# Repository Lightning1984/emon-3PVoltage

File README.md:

emon-3PVoltage
==============

Open Energy Monitoring 3 Phase Voltage Sensing Hardware with optoisolated I²C Interface

Images of the finished device can be found here:
<table style="width:194px;"><tr><td align="center" style="height:194px;background:url(https://www.gstatic.com/pwa/s/v/lighthousefe_241.01/transparent_album_background.gif) no-repeat left"></td></tr><tr><td style="text-align:center;font-family:arial,sans-serif;font-size:11px"><a href="https://picasaweb.google.com/rdobroun/Emon3PVoltage?authuser=0&feat=embedwebsite" style="color:#4D4D4D;font-weight:bold;text-decoration:none;">Emon3PVoltage</a></td></tr></table>

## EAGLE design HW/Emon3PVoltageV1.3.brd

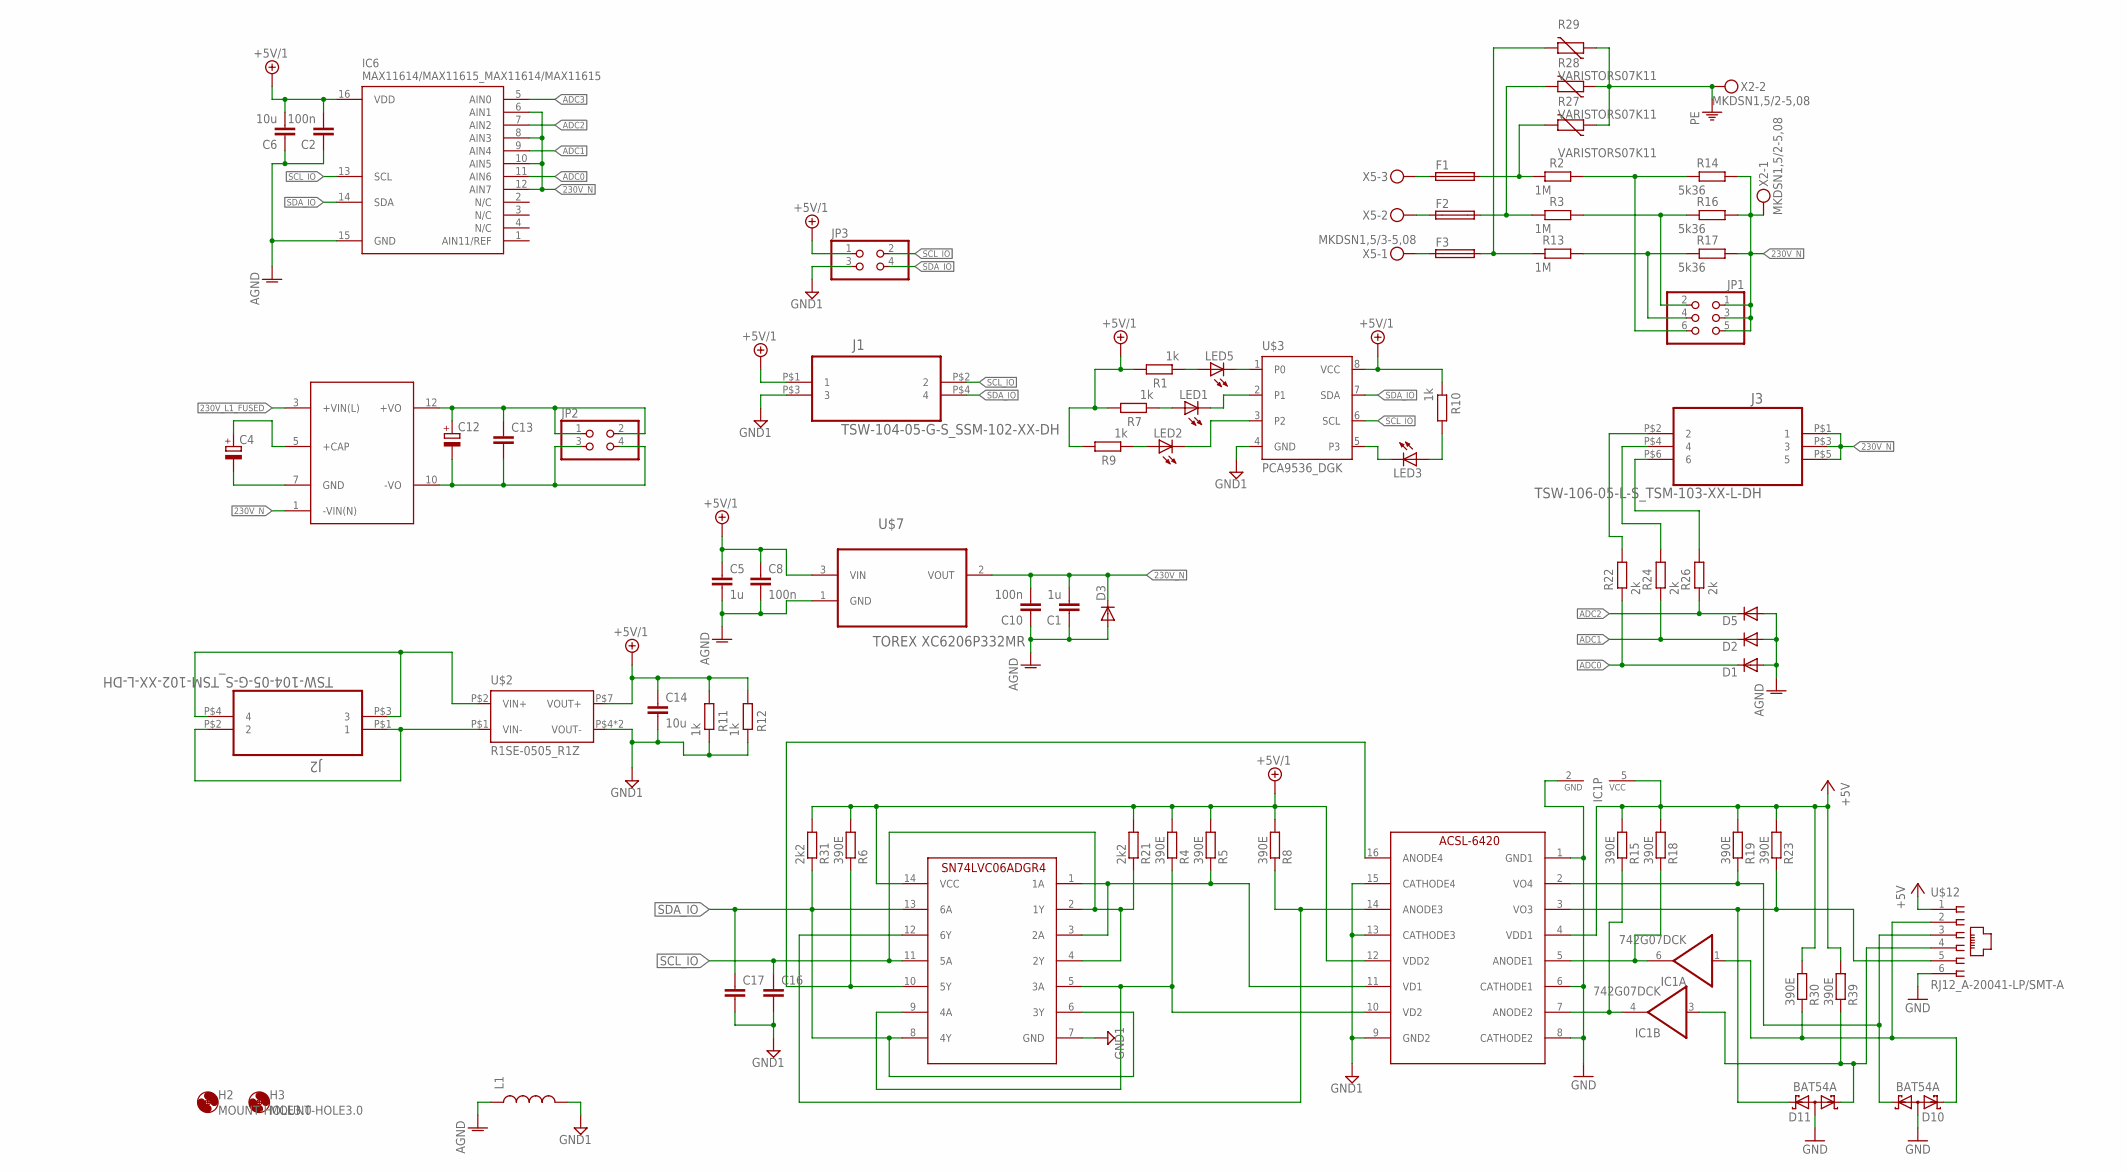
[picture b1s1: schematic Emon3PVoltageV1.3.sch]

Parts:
C1, C5: 1u; C0805
C2, C8, C10: 100n; C0805
C4: CPOL-EUE5-13; E5-13
C6, C14: 10u; C0805
C12: CPOL-EUE5-10.5; E5-10,5
C13, C16, C17: C-EUC0805; C0805
D1, D2, D3, D5: DIODE-SOD523; SOD523
D10, D11: BAT54A; SOT23
F1, F2, F3: TE5
H2, H3: MOUNT-HOLE3.0; 3,0
IC1: 742G07DCK; SC70-6
IC6: MAX11614/MAX11615_MAX11614/MAX11615; QSOP16_2
J1: TSW-104-05-G-S_SSM-102-XX-DH; SAMTEC_SSM-102-XX-DH
J2: TSW-104-05-G-S_TSM-102-XX-L-DH; SAMTEC_TSM-102-XX-L-DH
J3: TSW-106-05-L-S_TSM-103-XX-L-DH; SAMTEC_TSM-103-XX-L-DH
JP1: PINHD-2X3; 2X03
JP2, JP3: PINHD-2X2; 2X02
L1: INDUCTOR0805; 0805
LED1, LED2, LED3, LED5: LEDCHIPLED_1206; CHIPLED_1206
R1, R7, R9, R10, R11, R12: 1k; R1206
R2, R3, R13: 1M; 0207/12
R4, R5, R6, R8, R15, R18, R19, R23, R30, R39: 390E; R1206
R14, R16, R17: 5k36; R1206
R21, R31: 2k2; R1206
R22, R24, R26: 2k; R1206
R27, R28, R29: VARISTORS07K11; S07K11
U$1: LS03-15BXXSR2; LS03
U$2: R1SE-0505_R1Z; R1Z
U$3: PCA9536_DGK; DGK_S-PDSO-G8
U$7: TOREX XC6206P332MR; SOT95P237X112-3N
U$10: ACSL-6420; SO16
U$11: SN74LVC06ADRG4; SO-14
U$12: RJ12_A-20041-LP/SMT-A; A-2004-1-LP-SMT-B
X2: MKDSN1,5/2-5,08
X5: MKDSN1,5/3-5,08

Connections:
230V_L1_FUSED: F1.2, R2.2, R27.2, U$1.3 (+VIN(L))
230V_N: C1.2, C10.2, D3.C, IC6.6 (AIN1), IC6.8 (AIN3), IC6.10 (AIN5), IC6.12 (AIN7), J3.P$1 (1), J3.P$3 (3), J3.P$5 (5), JP1.1, JP1.3, JP1.5, R14.1, R16.1, R17.1, U$1.1 (-VIN(N)), U$7.2 (VOUT), X2.1
+5V: IC1.5 (VCC), R15.2, R18.2, R19.2, R23.2, R30.2, R39.2, U$10.4 (VDD1), U$12.1
+5V/1: C2.2, C5.1, C6.2, C8.1, C14.1, IC6.16 (VDD), J1.P$1 (1), JP3.1, R1.1, R4.2, R5.2, R6.2, R7.1, R8.2, R9.1, R10.2, R11.1, R12.1, R21.2, R31.2, U$2.P$7 (VOUT+), U$3.8 (VCC), U$7.3 (VIN), U$10.12 (VDD2), U$11.14 (VCC)
ADC0: D1.C, IC6.11 (AIN6), R22.2
ADC1: D2.C, IC6.9 (AIN4), R24.2
ADC2: D5.C, IC6.7 (AIN2), R26.2
ADC3: IC6.5 (AIN0)
AGND: C1.1, C2.1, C5.2, C6.1, C8.2, C10.1, D1.A, D2.A, D3.A, D5.A, IC6.15 (GND), L1.1, U$7.1 (GND)
GND: D10.3 (AA), D11.3 (AA), IC1.2 (GND), U$10.1 (GND1), U$10.6 (CATHODE1), U$10.8 (CATHODE2), U$12.6
GND1: C14.2, C16.2, C17.2, J1.P$3 (3), JP3.3, L1.2, R11.2, R12.2, U$2.P$4 (VOUT-), U$2.P$5 (VOUT-), U$3.4 (GND), U$10.9 (GND2), U$10.13 (CATHODE3), U$10.15 (CATHODE4), U$11.7 (GND)
unnamed: IC1.6 (O), R18.1, U$10.5 (ANODE1)
unnamed: LED3.C, U$3.5 (P3)
unnamed: C4.+, U$1.5 (+CAP)
unnamed: J3.P$2 (2), R22.1
unnamed: LED5.A, R1.2
unnamed: LED2.A, R9.2
unnamed: LED1.A, R7.2
unnamed: R5.1, U$10.11 (VD1), U$11.1 (1A), U$11.3 (2A)
unnamed: F2.2, R3.2, R28.2
unnamed: IC1.4 (O), R15.1, U$10.7 (ANODE2)
unnamed: F3.2, R13.2, R29.2
unnamed: J2.P$3 (3), J2.P$4 (4), U$2.P$2 (VIN+)
unnamed: JP1.2, R3.1, R16.2
unnamed: J2.P$1 (1), J2.P$2 (2), U$2.P$1 (VIN-)
unnamed: F3.1, X5.1
unnamed: R4.1, U$10.10 (VD2), U$11.5 (3A), U$11.9 (4A)
unnamed: F2.1, X5.2
unnamed: F1.1, X5.3
unnamed: C4.-, U$1.7 (GND)
unnamed: J3.P$6 (6), R26.1
unnamed: C12.-, C13.2, JP2.3, JP2.4, U$1.10 (-VO)
unnamed: C12.+, C13.1, JP2.1, JP2.2, U$1.12 (+VO)
unnamed: J3.P$4 (4), R24.1
unnamed: LED5.C, U$3.1 (P0)
unnamed: JP1.4, R13.1, R17.2
unnamed: LED1.C, U$3.2 (P1)
unnamed: R6.1, U$10.16 (ANODE4), U$11.10 (5Y)
unnamed: R8.1, U$10.14 (ANODE3), U$11.12 (6Y)
unnamed: JP1.6, R2.1, R14.2
unnamed: LED2.C, U$3.3 (P2)
unnamed: LED3.A, R10.1
PE: R27.1, R28.1, R29.1, X2.2
SCL_IO: C16.1, IC6.13 (SCL), J1.P$2 (2), JP3.2, R21.1, U$3.6 (SCL), U$11.2 (1Y), U$11.4 (2Y), U$11.11 (5A)
SCL_RX_UC: D10.1 (K1), R19.1, U$10.2 (VO4), U$12.3
SCL_TX_UC: D10.2 (K2), IC1.1 (I), R30.1, U$12.2
SDA_IO: C17.1, IC6.14 (SDA), J1.P$4 (4), JP3.4, R31.1, U$3.7 (SDA), U$11.6 (3Y), U$11.8 (4Y), U$11.13 (6A)
SDA_RY_UC: D11.2 (K2), R23.1, U$10.3 (VO3), U$12.5
SDA_TY_UC: D11.1 (K1), IC1.3 (I), R39.1, U$12.4

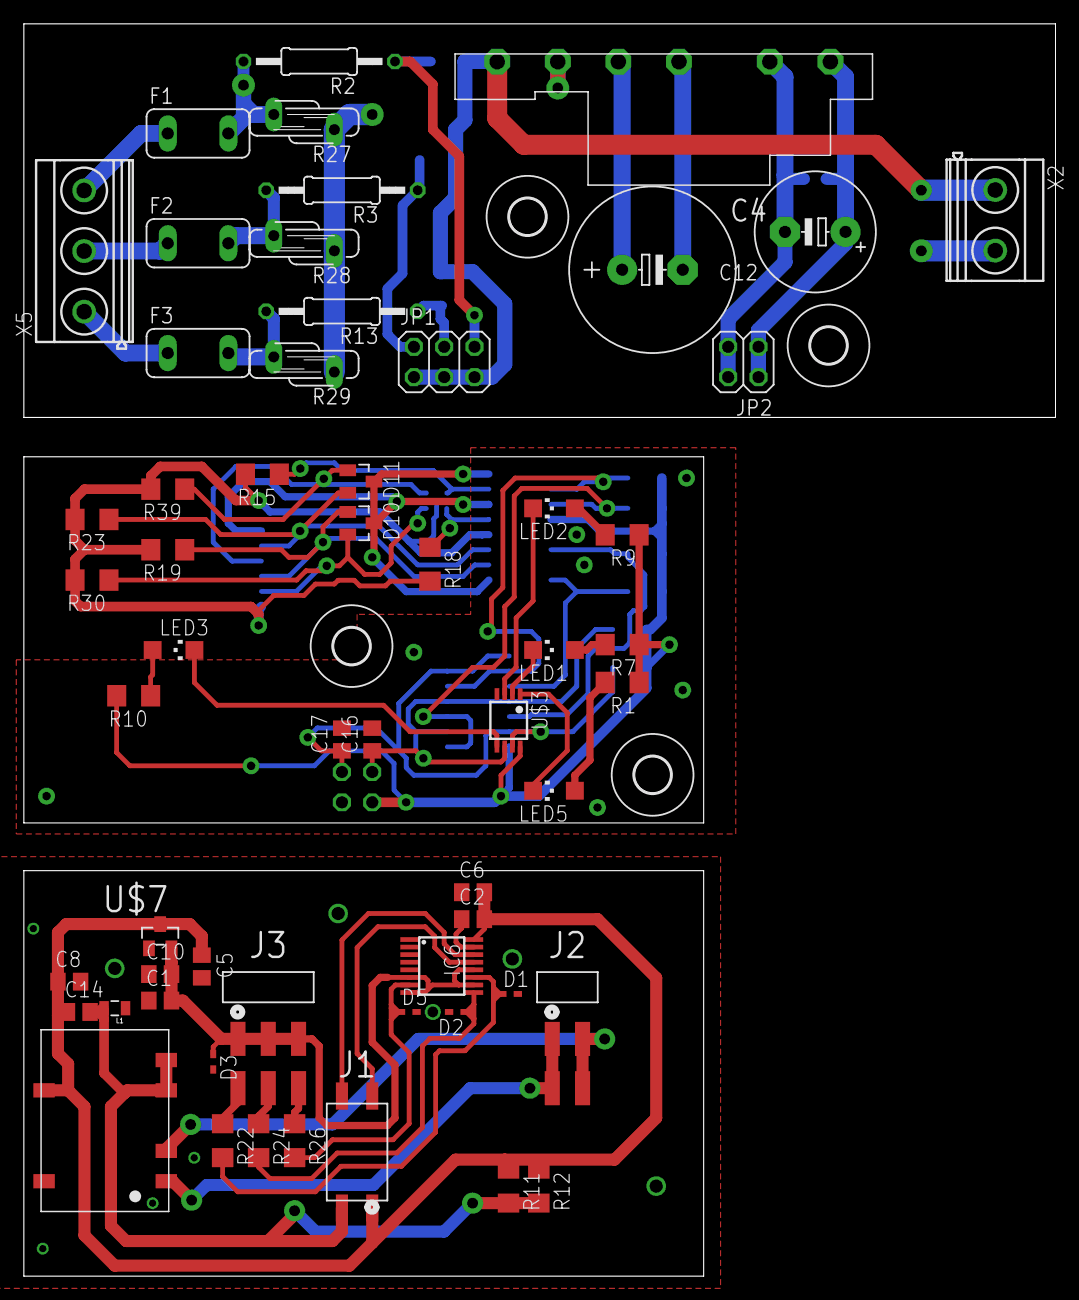
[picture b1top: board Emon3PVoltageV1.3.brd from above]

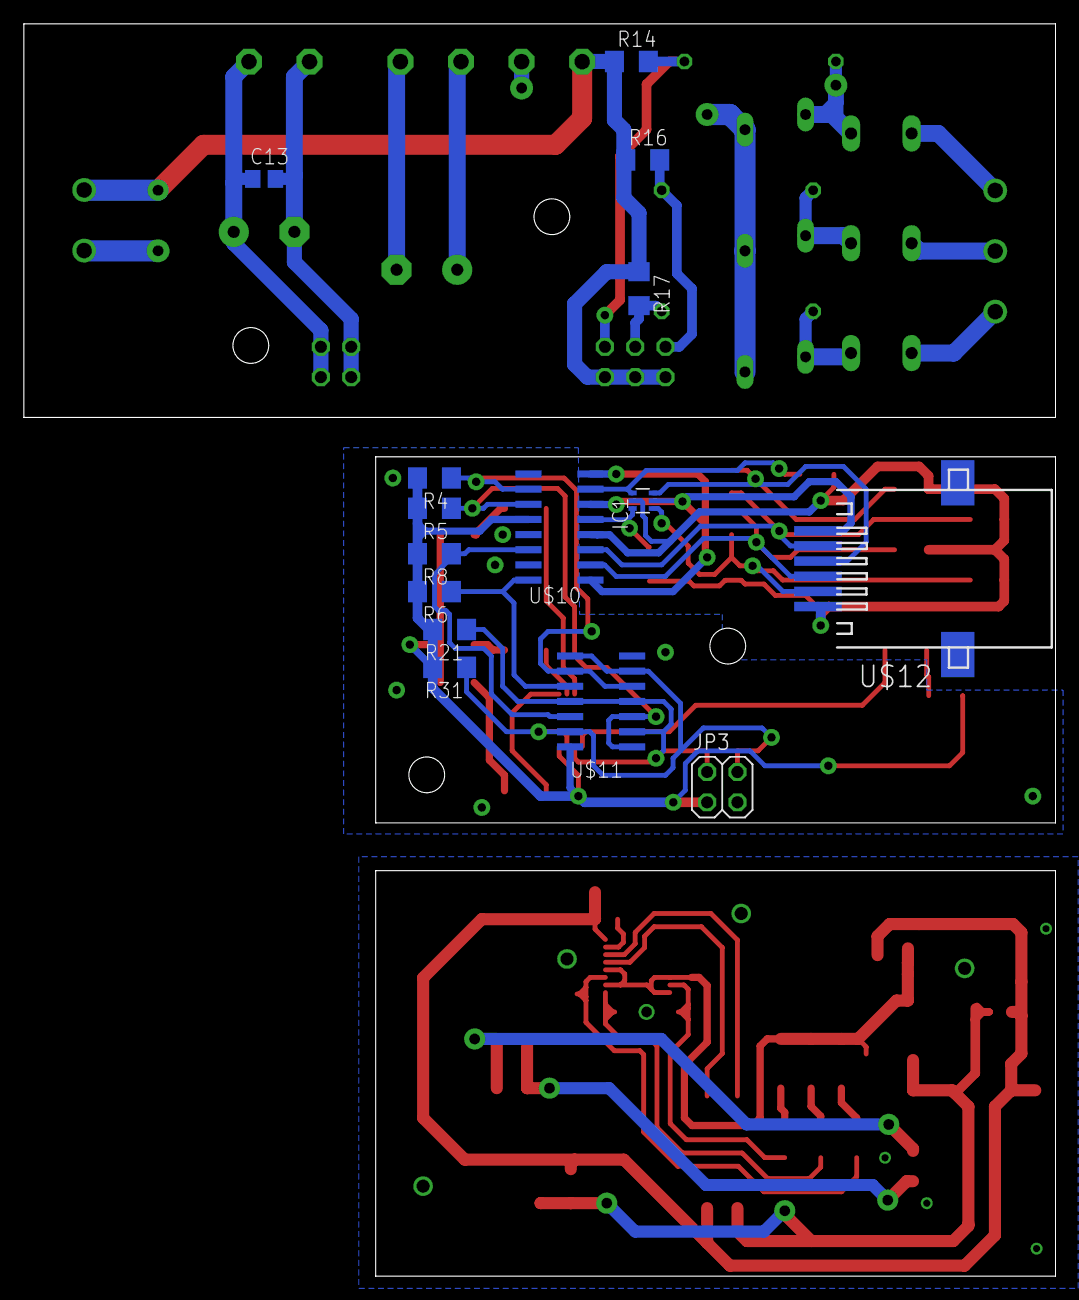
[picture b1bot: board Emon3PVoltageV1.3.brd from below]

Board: 2 copper layers, 86.5 x 105.0 mm, 77 parts (15 on the bottom side), 48 nets.

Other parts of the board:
H1, H4: MOUNT-HOLE3.0; 3,0

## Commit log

2014-06-12 Update LICENSE
2014-06-12 added brd and schematic files
2014-06-12 Added voltage divider calculation
2014-06-12 Update README.md
    Images of the finished device can be seen under:

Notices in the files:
HW/Emon3PVoltageV1.3.brd:
EmonRPi by Rupert Dobrounig is licensed under a
Creative Commons Attribution-NonCommercial-
